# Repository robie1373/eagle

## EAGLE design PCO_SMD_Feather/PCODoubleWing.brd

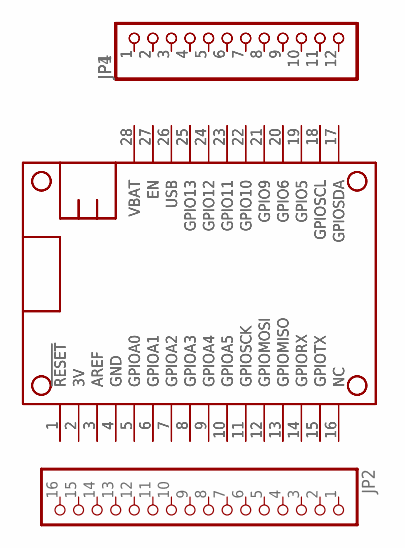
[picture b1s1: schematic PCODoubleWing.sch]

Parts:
JP1, JP4: HEADER-1X1276MIL; 1X12_ROUND_76MIL
JP2: HEADER-1X16_76MIL; 1X16_ROUND_76MIL
MS1, MS2: FEATHERWING_NODIM; FEATHERWING_DIM

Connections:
3V: MS1.2 (3V), MS2.2 (3V)
GND: MS1.4 (GND), MS2.4 (GND)
unnamed: JP1.2, JP4.2
unnamed: JP1.4, JP4.4
unnamed: JP1.5, JP4.5
unnamed: MS1.10 (GPIOA5), MS2.10 (GPIOA5)
unnamed: MS1.6 (GPIOA1), MS2.6 (GPIOA1)
unnamed: MS1.5 (GPIOA0), MS2.5 (GPIOA0)
unnamed: MS1.3 (AREF), MS2.3 (AREF)
unnamed: MS1.1 (!RESET), MS2.1 (!RESET)
unnamed: JP1.6, JP4.6
unnamed: JP1.7, JP4.7
unnamed: JP1.8, JP4.8
unnamed: JP1.9, JP4.9
unnamed: JP1.10, JP4.10
unnamed: JP1.11, JP4.11
unnamed: JP1.12, JP4.12
unnamed: JP1.1, JP4.1
unnamed: MS1.27 (EN), MS2.27 (EN)
unnamed: JP1.3, JP4.3
unnamed: MS1.25 (GPIO13), MS2.25 (GPIO13)
unnamed: MS1.24 (GPIO12), MS2.24 (GPIO12)
unnamed: MS1.23 (GPIO11), MS2.23 (GPIO11)
unnamed: MS1.22 (GPIO10), MS2.22 (GPIO10)
unnamed: MS1.21 (GPIO9), MS2.21 (GPIO9)
unnamed: MS1.20 (GPIO6), MS2.20 (GPIO6)
unnamed: MS1.19 (GPIO5), MS2.19 (GPIO5)
unnamed: MS1.18 (GPIOSCL), MS2.18 (GPIOSCL)
unnamed: MS1.17 (GPIOSDA), MS2.17 (GPIOSDA)
unnamed: MS1.7 (GPIOA2), MS2.7 (GPIOA2)
unnamed: MS1.8 (GPIOA3), MS2.8 (GPIOA3)
unnamed: MS1.9 (GPIOA4), MS2.9 (GPIOA4)
unnamed: MS1.11 (GPIOSCK), MS2.11 (GPIOSCK)
unnamed: MS1.12 (GPIOMOSI), MS2.12 (GPIOMOSI)
unnamed: MS1.13 (GPIOMISO), MS2.13 (GPIOMISO)
unnamed: MS1.14 (GPIORX), MS2.14 (GPIORX)
unnamed: MS1.15 (GPIOTX), MS2.15 (GPIOTX)
unnamed: MS1.16 (NC), MS2.16 (NC)
USB: MS1.26 (USB), MS2.26 (USB)
VBAT: MS1.28 (VBAT), MS2.28 (VBAT)

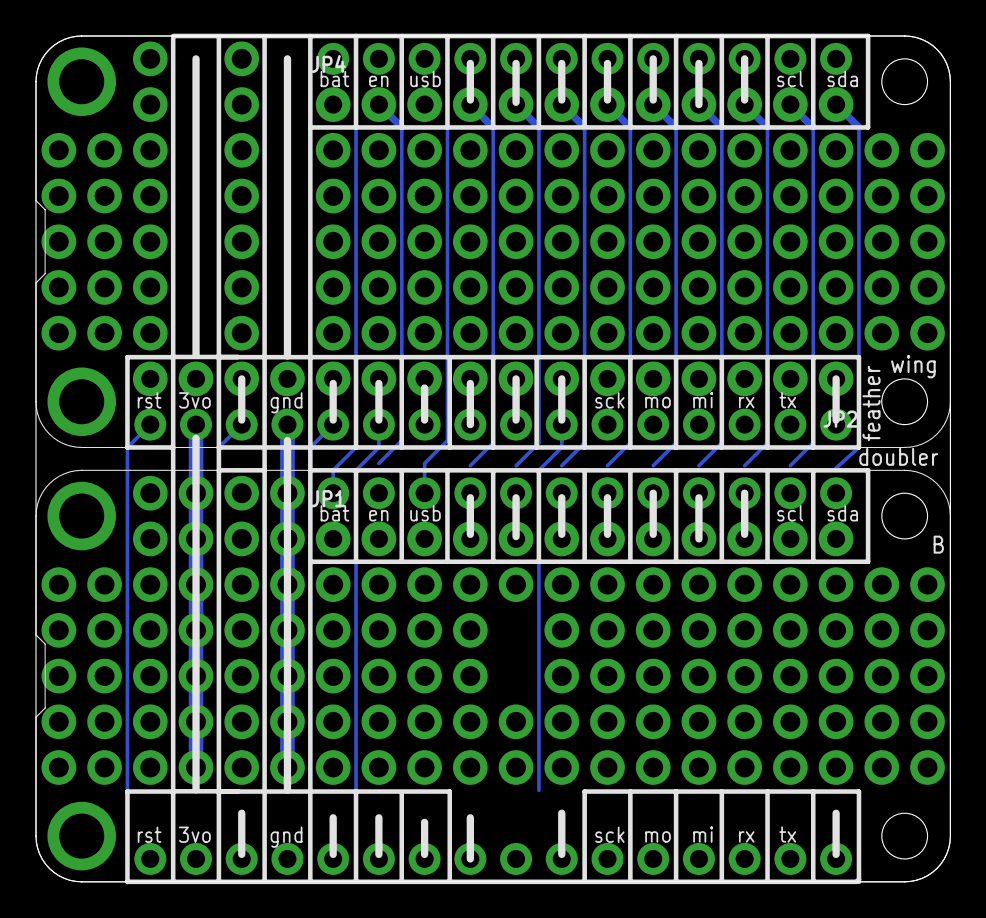
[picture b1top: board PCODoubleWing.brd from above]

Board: 2 copper layers, 50.8 x 47.0 mm, 5 parts (0 on the bottom side), 40 nets.

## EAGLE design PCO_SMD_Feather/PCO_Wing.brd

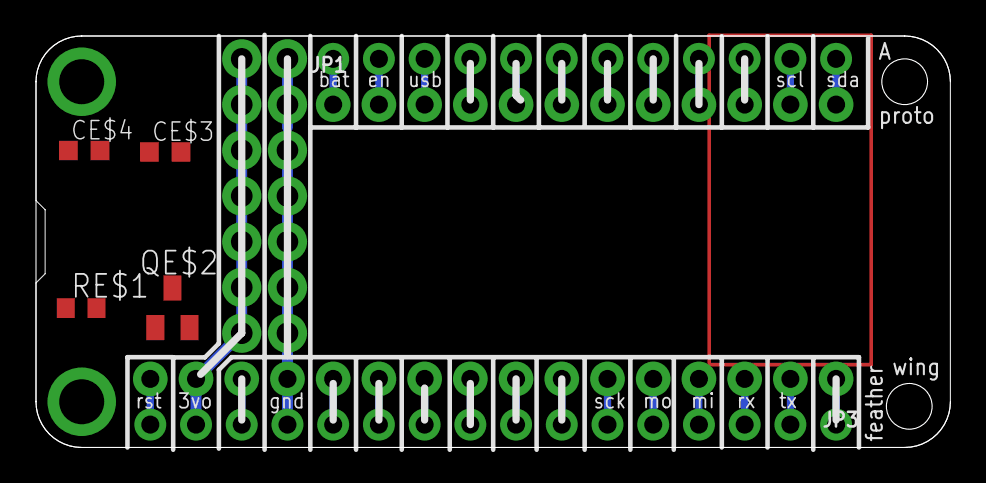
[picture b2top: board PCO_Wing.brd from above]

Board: 2 copper layers, 50.8 x 22.9 mm, 7 parts (0 on the bottom side), 28 nets.

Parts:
CE$3: 0.1 uF; C0603K
CE$4: 10 uF; C0603K
JP1: 1X12_ROUND_76MIL
JP3: 1X16_ROUND_76MIL
MS1: MICROSHIELD_NODIM; MICROSHIELD_DIM
QE$2: SOT23
RE$1: 68; R0603

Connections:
3V: JP3.15, MS1.2
AREF: JP3.14, MS1.3
GND: JP3.13, MS1.4
unnamed: JP1.2, MS1.27
unnamed: JP3.1, MS1.16
unnamed: JP1.4, MS1.25
unnamed: JP3.2, MS1.15
unnamed: JP1.5, MS1.24
unnamed: JP3.3, MS1.14
unnamed: JP3.4, MS1.13
unnamed: JP3.5, MS1.12
unnamed: JP3.6, MS1.11
unnamed: JP3.7, MS1.10
unnamed: JP3.8, MS1.9
unnamed: JP3.9, MS1.8
unnamed: JP3.10, MS1.7
unnamed: JP3.11, MS1.6
unnamed: JP3.12, MS1.5
unnamed: JP3.16, MS1.1
unnamed: JP1.6, MS1.23
unnamed: JP1.7, MS1.22
unnamed: JP1.8, MS1.21
unnamed: JP1.9, MS1.20
unnamed: JP1.10, MS1.19
unnamed: JP1.11, MS1.18
unnamed: JP1.12, MS1.17
USB: JP1.3, MS1.26
VBAT: JP1.1, MS1.28

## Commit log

2016-02-29 work so far
